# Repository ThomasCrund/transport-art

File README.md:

# Transport Art

This project is a wall-mounted transport map artwork.

The physical idea is:
- a black acrylic front layer cut as the outline of local streets
- rigid LED PCB sections mounted behind the acrylic
- flexible PCB links between sections at joints
- wall standoffs that space the whole assembly off the wall so the LEDs throw light onto the wall behind

The intent is to show live bus and light rail positions as light moving through the street network.

## Current Repository Layout

### Active work

- `CustomisableLEDStraight/`
  - Current straight LED PCB design work.
  - Uses WS2812-style addressable LEDs and connector-based chaining.

- `adaptor board/`
  - Adapter / interconnect board work related to the PCB connection system.

- `testingstencil/`
  - Stencil-related PCB project for assembly/testing.

- `transportmapwebhelper/`
  - Map planning assets and helper tooling.
  - Contains the street SVG and a React webapp used to inspect and edit the map layout, PCB placement, joints, and LED chains.

- `code/rust-realtime-vehicle/`
  - Rust service that fetches NSW GTFS realtime vehicle positions and exposes them over HTTP.
  - Currently serves `/positions` on port `3000`.

- `code/grpc-realtime-node/`
  - Earlier Node prototype for fetching GTFS realtime data.

### Old testing projects

These folders are old test projects and not the current design direction:

- `3332_16mm/`
- `3332_25mm_v2/`
- `5050_16mm/`
- `5050_20mm/`
- `5050_25mm/`
- `ConnectorsTesting/`

## Map / Planning Workflow

The map geometry appears to flow like this:

1. Street and layout artwork is created in Illustrator / DXF / SVG form.
2. `transportmapwebhelper/streetsv2consistentangles.svg` is parsed by `transportmapwebhelper/webapp/scripts/parse-svg.ts`.
3. That script generates `transportmapwebhelper/webapp/public/map_data.json`.
4. The React webapp loads that JSON and lets you inspect:
   - streets selected for LEDs
   - PCB segments
   - LED positions
   - joints between segments
   - logical LED chain routing
5. Chain assignments are saved to `transportmapwebhelper/webapp/public/chain_config.json`.

Based on the current saved data:

- `317` street paths are present
- `21` streets are marked as LED streets
- `86` PCB segments are defined
- `86` joints are defined
- `228` total LEDs are planned
- PCB segment sizes currently span `1` to `5` LEDs
- `9` logical LED chains are currently configured

## Webapp

The planning webapp lives in `transportmapwebhelper/webapp/`.

It has two parts:

- Vite/React frontend
- small Express API used to save `map_data.json` and `chain_config.json`

Useful files:

- `transportmapwebhelper/webapp/src/components/TransportMap.tsx`
- `transportmapwebhelper/webapp/src/hooks/useMapData.ts`
- `transportmapwebhelper/webapp/src/hooks/useChainConfig.ts`
- `transportmapwebhelper/webapp/server.js`

Typical local run:

```bash
cd transportmapwebhelper/webapp
npm install
npm run dev
```

That starts:

- the frontend dev server
- the local save/load API on port `3001`

## Realtime Vehicle Data

The most complete realtime data service currently in the repo is:

- `code/rust-realtime-vehicle/`

It:

- fetches NSW GTFS realtime vehicle positions
- currently requests both buses and CBD/South East light rail
- returns a simplified JSON list of vehicles with:
  - vehicle type
  - latitude / longitude
  - speed
  - bearing
  - route id

Typical local run:

```bash
cd code/rust-realtime-vehicle
cargo run
```

## CAD / Artwork Files

Top-level art and export files include:

- `streets.ai`
- `streets.dxf`
- `streetsv2consistentangles.ai`
- `streetsv2consistentangles.dxf`
- `final-lines.dxf`
- `final-linesv2.dxf`

There are also QGIS sidecar files:

- `lines-1.qmd`
- `lines-2.qmd`

## Current Gaps

From the current repo state, a few parts still appear to be incomplete or external to this repository:

- final controller firmware that drives the installed LEDs
- the mapping layer from live vehicle positions to specific PCB/LED indices
- 3D models for wall standoffs / mounting hardware
- final flexible PCB designs for all inter-joint links

## Notes

- Some transport API credentials are currently hardcoded in the prototype/realtime code and should eventually be moved to environment variables.
- The webapp and generated JSON files are currently the clearest representation of the planned wall layout.

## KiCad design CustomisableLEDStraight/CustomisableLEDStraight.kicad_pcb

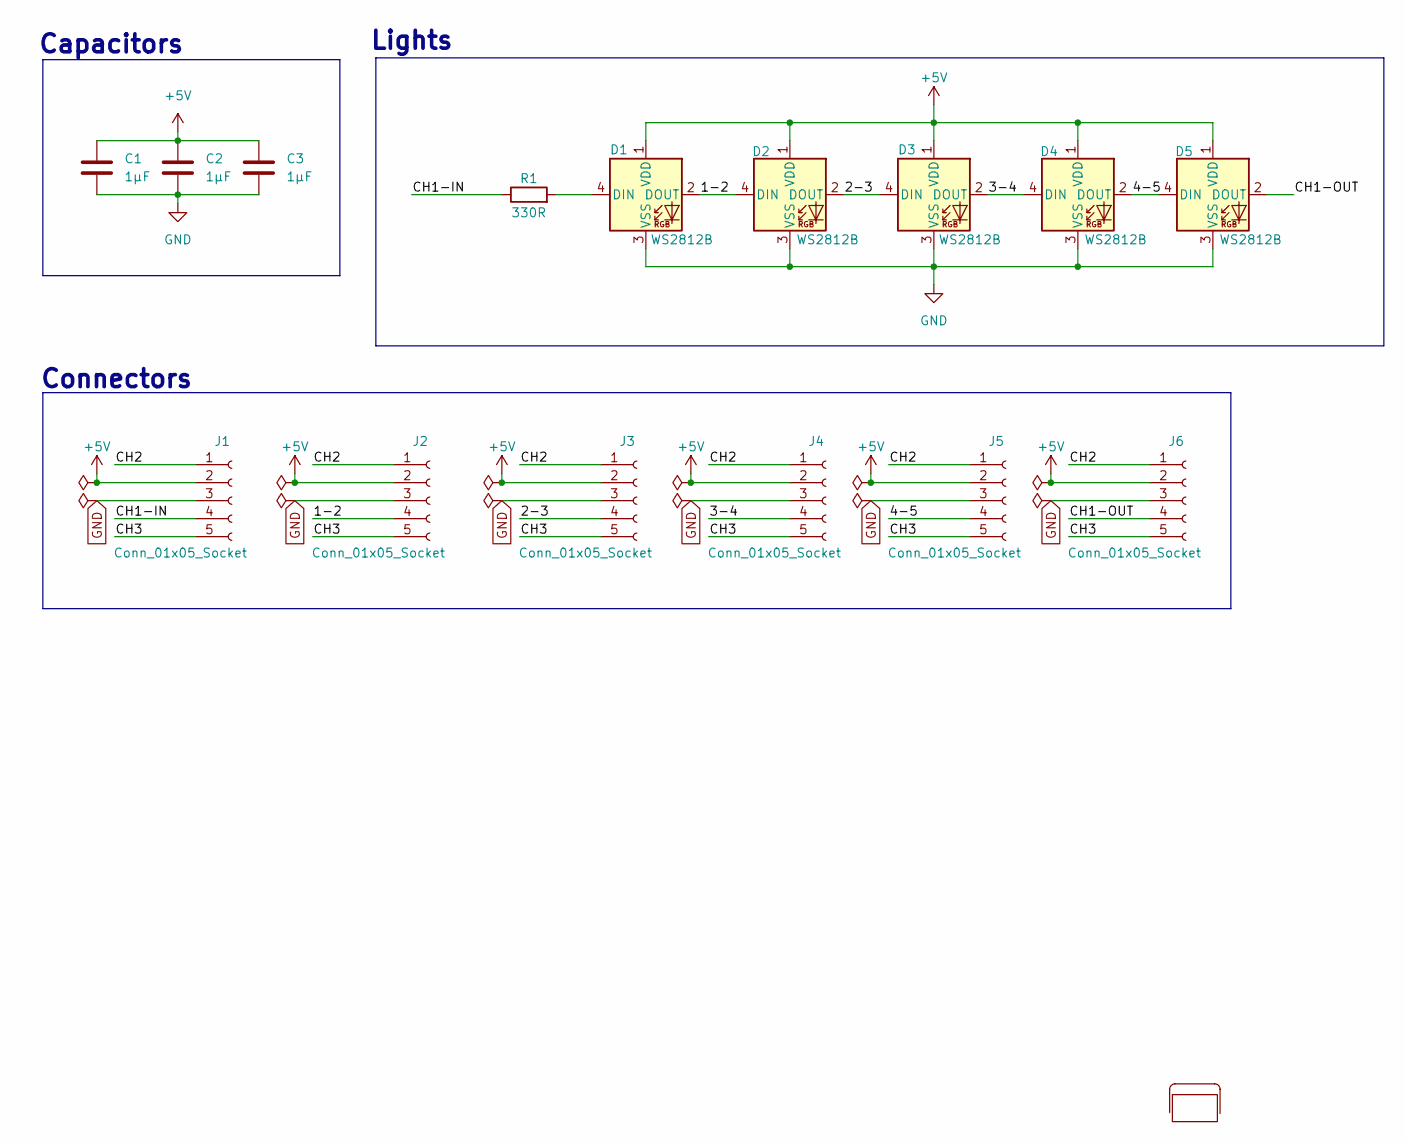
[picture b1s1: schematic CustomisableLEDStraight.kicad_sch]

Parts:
C1, C2, C3: 1µF; C_0603_1608Metric
D1, D2, D3, D4, D5: WS2812B; XL-3332RGBC-WS2812B
ESKI1: Eski_Logo
J1, J6: Conn_01x05_Socket; TransportMapConnector_half
J2, J3, J4, J5: Conn_01x05_Socket; TransportMapConnector
R1: 330R; R_0603_1608Metric

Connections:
+5V: C1.2, C2.2, C3.2, D1.1 (VDD), D2.1 (VDD), D3.1 (VDD), D4.1 (VDD), D5.1 (VDD), J1.2, J2.2, J3.2, J4.2, J5.2, J6.2
/1-2: D1.2 (DOUT), D2.4 (DIN), J2.4
/2-3: D2.2 (DOUT), D3.4 (DIN), J3.4
/3-4: D3.2 (DOUT), D4.4 (DIN), J4.4
/4-5: D4.2 (DOUT), D5.4 (DIN), J5.4
/CH1-IN: J1.4, R1.1
/CH1-OUT: D5.2 (DOUT), J6.4
/CH2: J1.1, J2.1, J3.1, J4.1, J5.1, J6.1
/CH3: J1.5, J2.5, J3.5, J4.5, J5.5, J6.5
GND: C1.1, C2.1, C3.1, D1.3 (VSS), D2.3 (VSS), D3.3 (VSS), D4.3 (VSS), D5.3 (VSS), J1.3, J2.3, J3.3, J4.3, J5.3, J6.3
unnamed: D1.4 (DIN), R1.2

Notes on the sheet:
Lights
Connectors
Capacitors

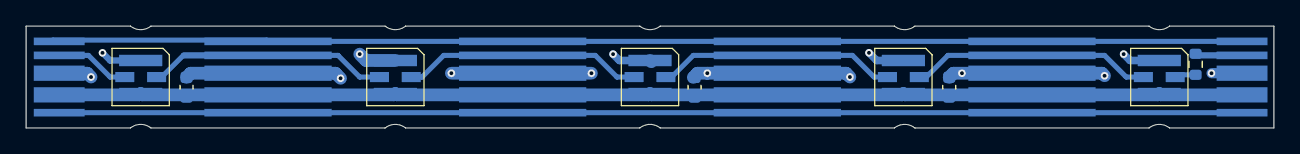
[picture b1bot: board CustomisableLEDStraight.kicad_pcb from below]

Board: 2 copper layers, 98.0 x 8.0 mm, 16 parts (15 on the bottom side), 11 nets.

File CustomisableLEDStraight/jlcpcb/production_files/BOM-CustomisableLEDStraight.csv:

Comment,Designator,Footprint,LCSC,Quantity
Conn_01x05_Socket,J2,TransportMapConnector,,1
Conn_01x05_Socket,J1,TransportMapConnector_half,,1
WS2812B,D5,XL-3332RGBC-WS2812B,,1
1µF,C2,C_0603_1608Metric,,1
WS2812B,D3,XL-3332RGBC-WS2812B,,1
WS2812B,D2,XL-3332RGBC-WS2812B,,1
1µF,C3,C_0603_1608Metric,,1
WS2812B,D4,XL-3332RGBC-WS2812B,,1
1µF,C1,C_0603_1608Metric,,1
WS2812B,D1,XL-3332RGBC-WS2812B,,1
330R,R1,R_0603_1608Metric,,1
Conn_01x05_Socket,J6,TransportMapConnector_half,,1
Conn_01x05_Socket,J5,TransportMapConnector,,1
Conn_01x05_Socket,J4,TransportMapConnector,,1
Conn_01x05_Socket,J3,TransportMapConnector,,1

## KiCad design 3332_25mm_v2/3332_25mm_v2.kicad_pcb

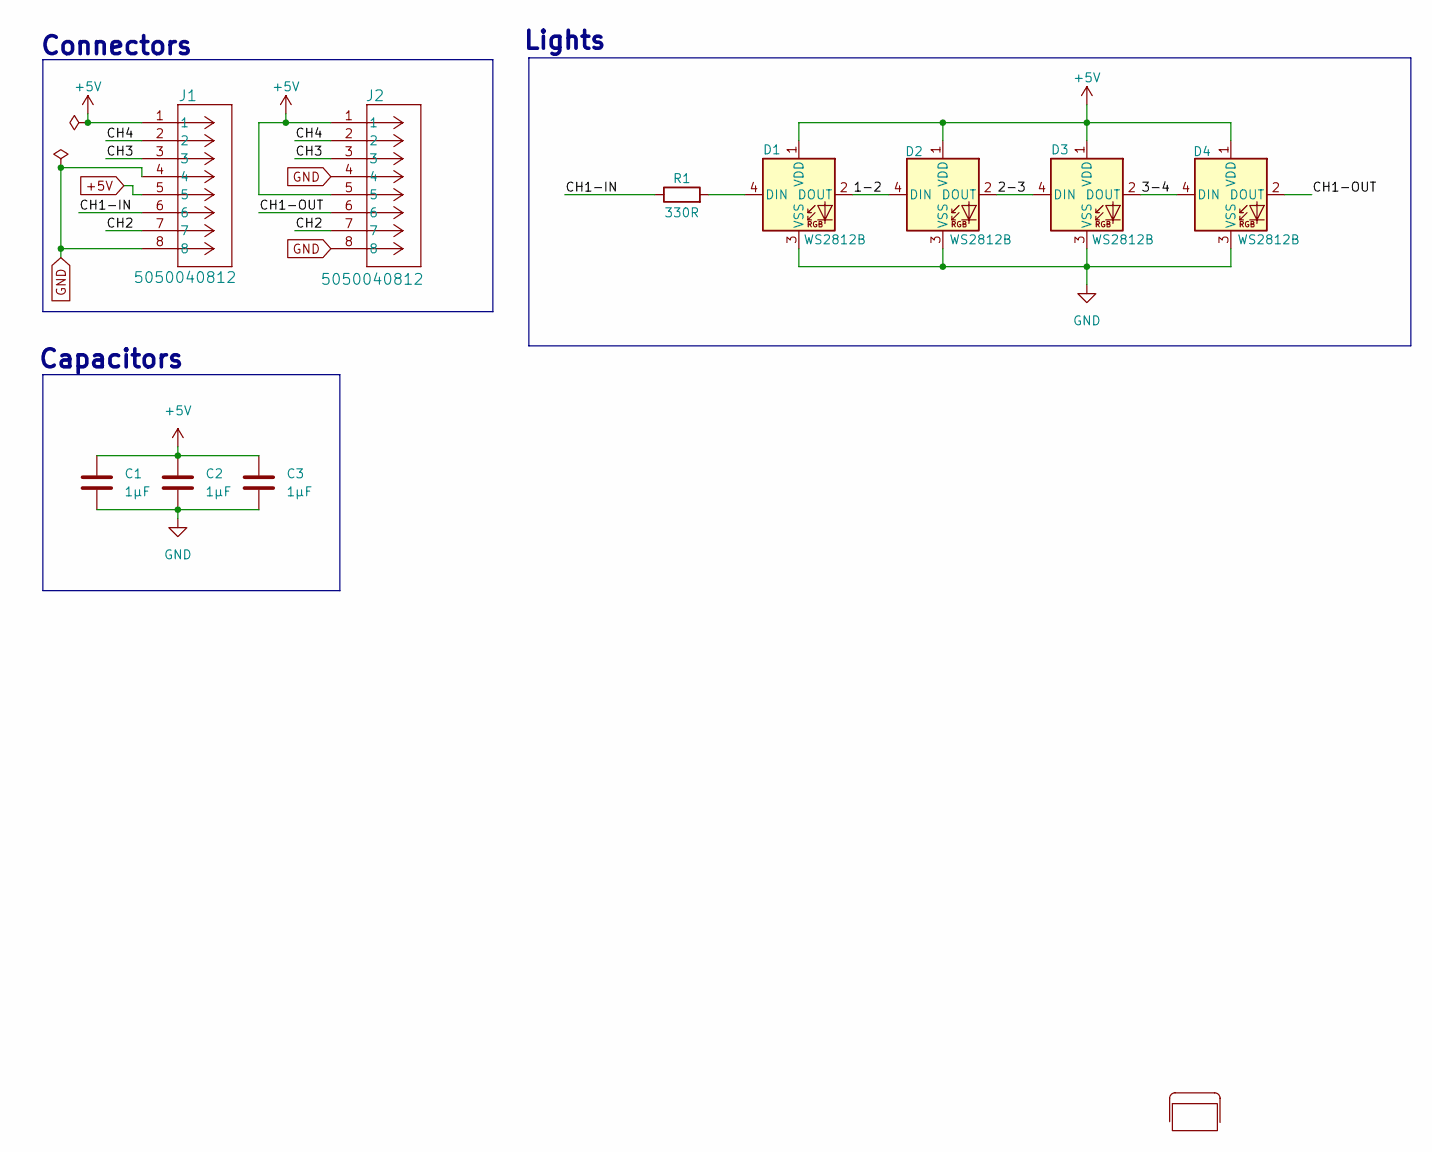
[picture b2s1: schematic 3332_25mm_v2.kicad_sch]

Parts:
C1, C2, C3: 1µF; C_0603_1608Metric
D1, D2, D3, D4: WS2812B; XL-3332RGBC-WS2812B
ESKI1: Eski_Logo
J1, J2: 5050040812; CONN8_505004-0812_MOL
R1: 330R; R_0603_1608Metric

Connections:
+5V: C1.2, C2.2, C3.2, D1.1 (VDD), D2.1 (VDD), D3.1 (VDD), D4.1 (VDD), J1.1, J1.5, J2.1, J2.5
/1-2: D1.2 (DOUT), D2.4 (DIN)
/2-3: D2.2 (DOUT), D3.4 (DIN)
/3-4: D3.2 (DOUT), D4.4 (DIN)
/CH1-IN: J1.6, R1.1
/CH1-OUT: D4.2 (DOUT), J2.6
/CH2: J1.7, J2.7
/CH3: J1.3, J2.3
/CH4: J1.2, J2.2
GND: C1.1, C2.1, C3.1, D1.3 (VSS), D2.3 (VSS), D3.3 (VSS), D4.3 (VSS), J1.4, J1.8, J2.4, J2.8
unnamed: D1.4 (DIN), R1.2

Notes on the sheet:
Connectors
Lights
Capacitors

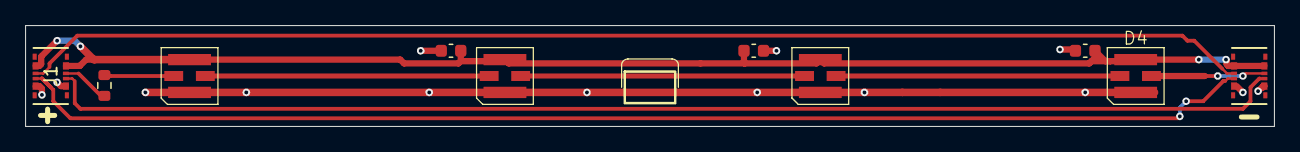
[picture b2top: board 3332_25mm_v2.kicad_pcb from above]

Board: 2 copper layers, 99.0 x 8.0 mm, 11 parts (0 on the bottom side), 11 nets.

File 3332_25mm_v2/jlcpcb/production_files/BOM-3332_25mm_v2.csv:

Comment,Designator,Footprint,LCSC,Quantity
5050040812,J2,CONN8_505004-0812_MOL,,1
5050040812,J1,CONN8_505004-0812_MOL,,1
1µF,C2,C_0603_1608Metric,,1
WS2812B,D3,XL-3332RGBC-WS2812B,,1
WS2812B,D2,XL-3332RGBC-WS2812B,,1
1µF,C3,C_0603_1608Metric,,1
WS2812B,D4,XL-3332RGBC-WS2812B,,1
1µF,C1,C_0603_1608Metric,,1
WS2812B,D1,XL-3332RGBC-WS2812B,,1
330R,R1,R_0603_1608Metric,,1

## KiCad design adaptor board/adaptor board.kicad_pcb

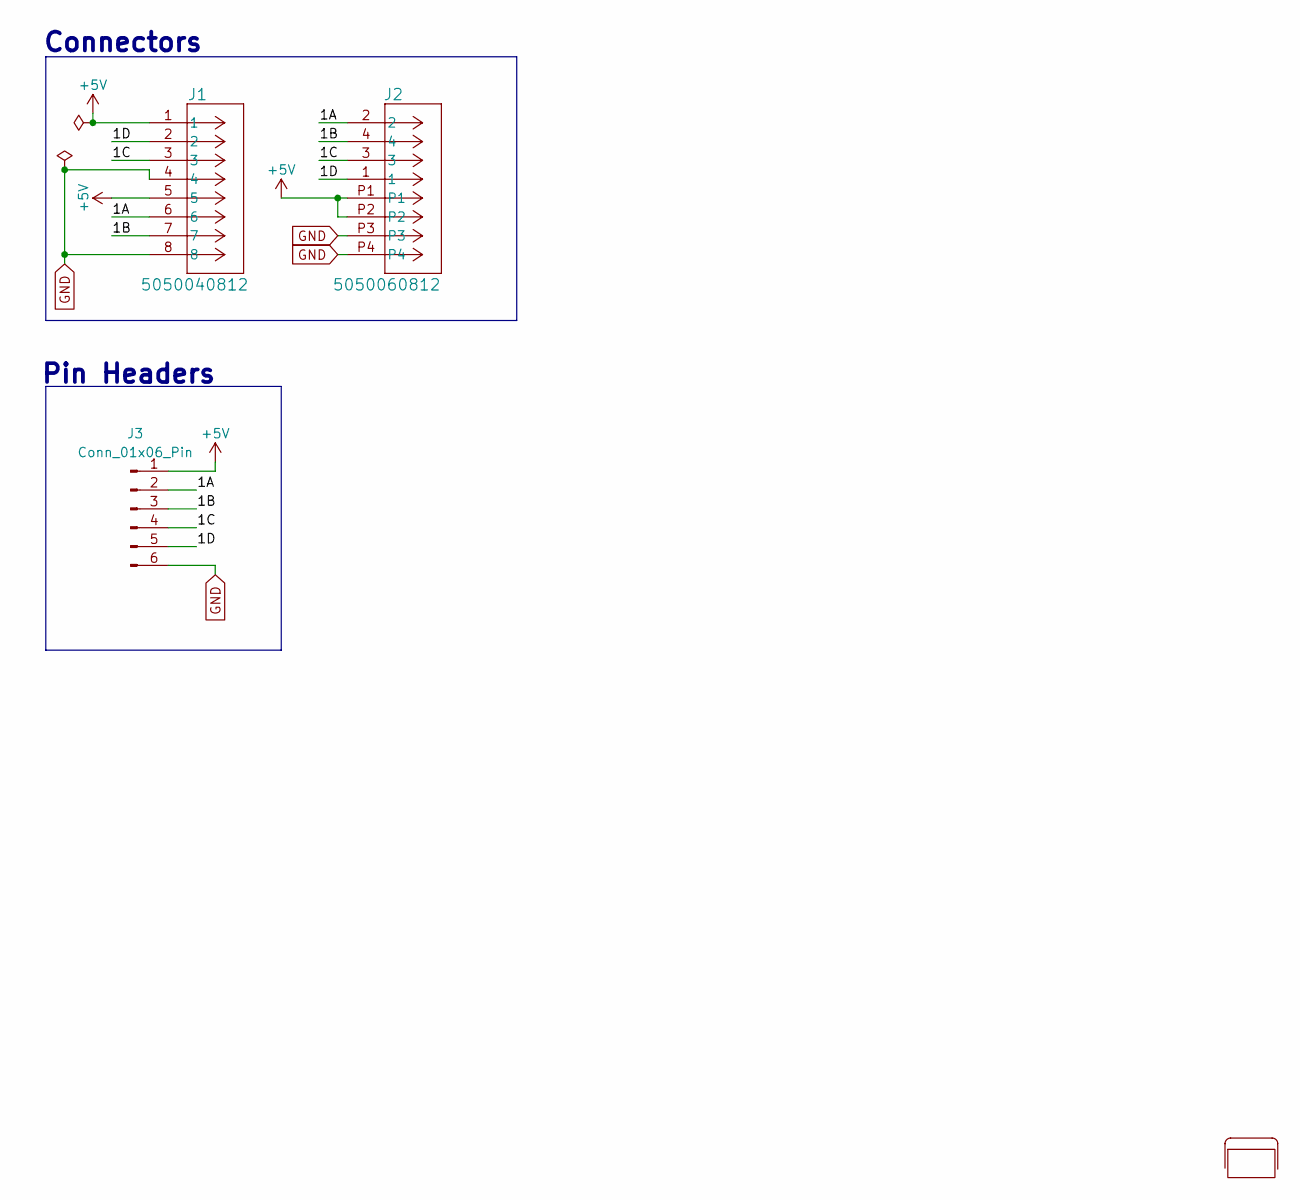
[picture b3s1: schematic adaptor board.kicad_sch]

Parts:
ESKI1: Eski_Logo
J1: 5050040812; CONN8_505004-0812_MOL
J2: 5050060812; CONN_505006-0812_MOL
J3: Conn_01x06_Pin; PinHeader_1x06_P2.54mm_Vertical

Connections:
+5V: J1.1, J1.5, J2.P1, J2.P2, J3.1
/1A: J1.6, J2.2, J3.2
/1B: J1.7, J2.4, J3.3
/1C: J1.3, J2.3, J3.4
/1D: J1.2, J2.1, J3.5
GND: J1.4, J1.8, J2.P3, J2.P4, J3.6

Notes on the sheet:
Pin Headers
Connectors

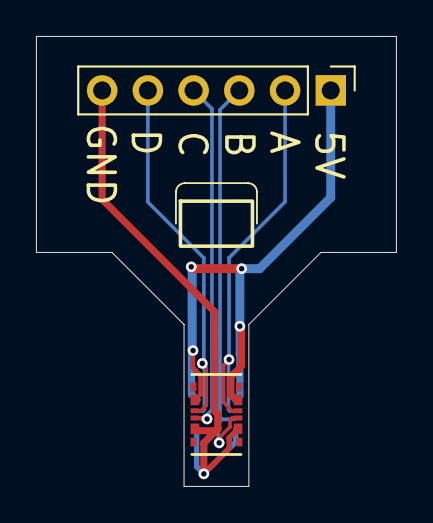
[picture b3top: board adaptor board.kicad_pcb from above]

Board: 2 copper layers, 20.0 x 25.0 mm, 4 parts (1 on the bottom side), 6 nets.

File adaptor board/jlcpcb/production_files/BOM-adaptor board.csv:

Comment,Designator,Footprint,LCSC,Quantity
5050040812,J1,CONN8_505004-0812_MOL,C724121,1
5050060812,J2,CONN_505006-0812_MOL,C779875,1
Conn_01x06_Pin,J3,PinHeader_1x06_P2.54mm_Vertical,,1

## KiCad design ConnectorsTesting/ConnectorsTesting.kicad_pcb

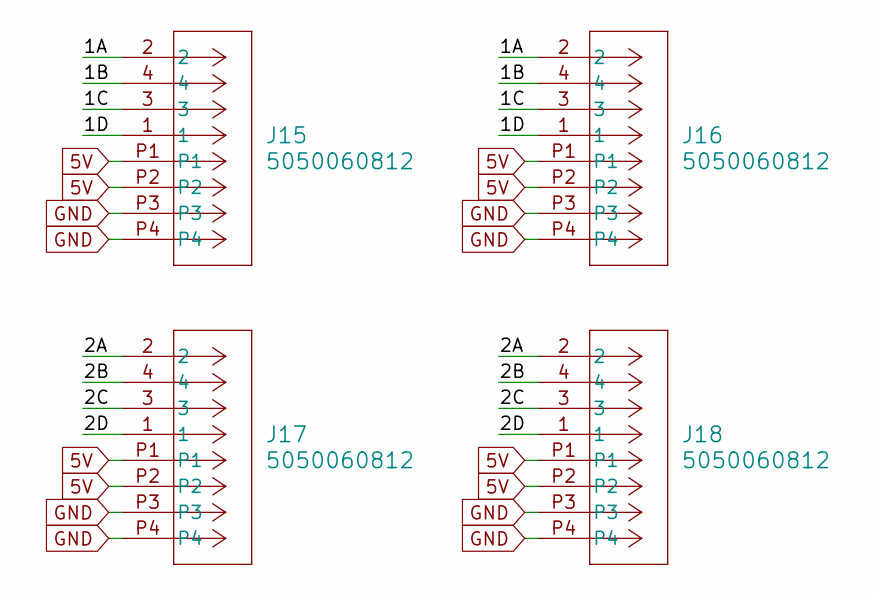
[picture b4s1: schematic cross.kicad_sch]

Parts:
J15, J16, J17, J18: 5050060812; CONN_505006-0812_MOL

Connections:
5V: J15.P1, J15.P2, J16.P1, J16.P2, J17.P1, J17.P2, J18.P1, J18.P2; also elsewhere on the board
/Cross/1A: J15.2, J16.2
/Cross/1B: J15.4, J16.4
/Cross/1C: J15.3, J16.3
/Cross/1D: J15.1, J16.1
/Cross/2A: J17.2, J18.2
/Cross/2B: J17.4, J18.4
/Cross/2C: J17.3, J18.3
/Cross/2D: J17.1, J18.1
GND: J15.P3, J15.P4, J16.P3, J16.P4, J17.P3, J17.P4, J18.P3, J18.P4; also elsewhere on the board

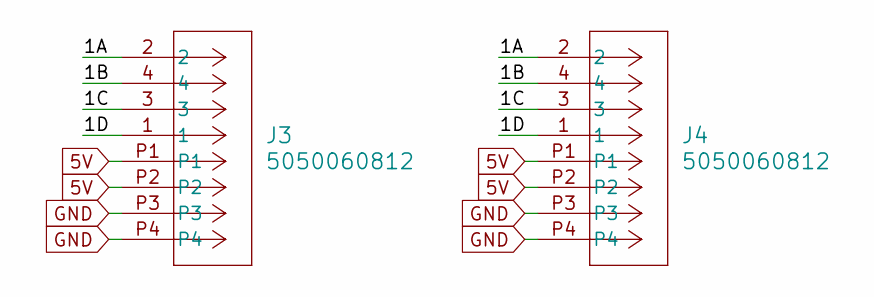
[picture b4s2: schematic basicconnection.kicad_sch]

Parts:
J3, J4: 5050060812; CONN_505006-0812_MOL

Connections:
5V: J3.P1, J3.P2, J4.P1, J4.P2; also elsewhere on the board
/Basic1-1/1A: J3.2, J4.2
/Basic1-1/1B: J3.4, J4.4
/Basic1-1/1C: J3.3, J4.3
/Basic1-1/1D: J3.1, J4.1
GND: J3.P3, J3.P4, J4.P3, J4.P4; also elsewhere on the board

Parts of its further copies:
J19, J20, J21, J22, J23, J24, J25, J26: 5050060812; CONN_505006-0812_MOL

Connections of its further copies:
5V: J19.P1, J19.P2, J20.P1, J20.P2, J21.P1, J21.P2, J22.P1, J22.P2, J23.P1, J23.P2, J24.P1, J24.P2, J25.P1, J25.P2, J26.P1, J26.P2; also elsewhere on the board
/Basic1-1-curve1/1A: J19.2, J20.2
/Basic1-1-curve1/1B: J19.4, J20.4
/Basic1-1-curve1/1C: J19.3, J20.3
/Basic1-1-curve1/1D: J19.1, J20.1
/Basic1-1-curve-2/1A: J21.2, J22.2
/Basic1-1-curve-2/1B: J21.4, J22.4
/Basic1-1-curve-2/1C: J21.3, J22.3
/Basic1-1-curve-2/1D: J21.1, J22.1
/Basic1-2-extension2/1A: J25.2, J26.2
/Basic1-2-extension2/1B: J25.4, J26.4
/Basic1-2-extension2/1C: J25.3, J26.3
/Basic1-2-extension2/1D: J25.1, J26.1
/Basic1-2-extension/1A: J23.2, J24.2
/Basic1-2-extension/1B: J23.4, J24.4
/Basic1-2-extension/1C: J23.3, J24.3
/Basic1-2-extension/1D: J23.1, J24.1
GND: J19.P3, J19.P4, J20.P3, J20.P4, J21.P3, J21.P4, J22.P3, J22.P4, J23.P3, J23.P4, J24.P3, J24.P4, J25.P3, J25.P4, J26.P3, J26.P4; also elsewhere on the board

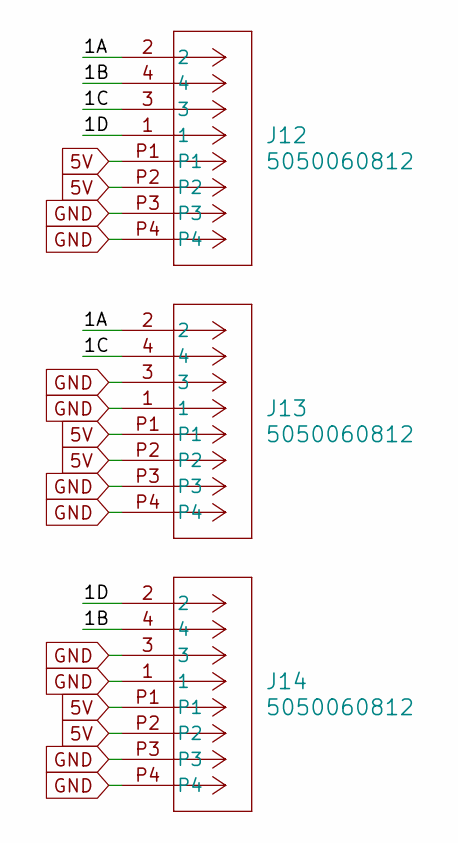
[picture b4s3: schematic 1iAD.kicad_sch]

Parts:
J12, J13, J14: 5050060812; CONN_505006-0812_MOL

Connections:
5V: J12.P1, J12.P2, J13.P1, J13.P2, J14.P1, J14.P2; also elsewhere on the board
/1Input;Output(A,D)/1A: J12.2, J13.2
/1Input;Output(A,D)/1B: J12.4, J14.4
/1Input;Output(A,D)/1C: J12.3, J13.4
/1Input;Output(A,D)/1D: J12.1, J14.2
GND: J12.P3, J12.P4, J13.1, J13.3, J13.P3, J13.P4, J14.1, J14.3, J14.P3, J14.P4; also elsewhere on the board

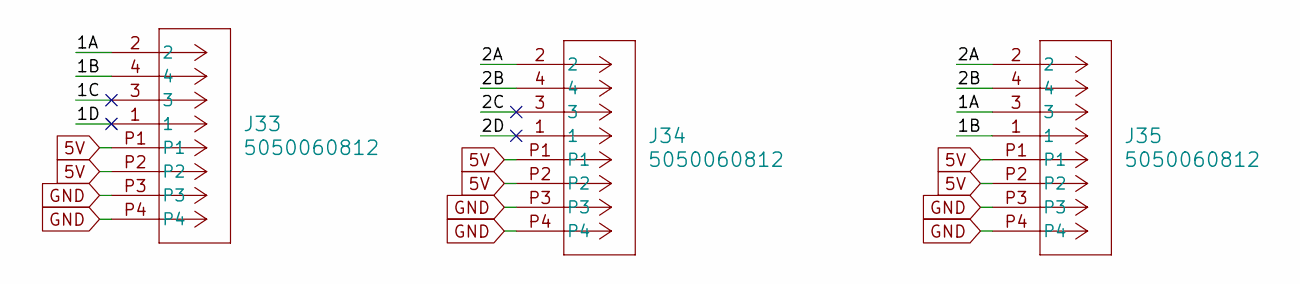
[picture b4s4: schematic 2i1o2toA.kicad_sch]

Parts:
J33, J34, J35: 5050060812; CONN_505006-0812_MOL

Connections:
5V: J33.P1, J33.P2, J34.P1, J34.P2, J35.P1, J35.P2; also elsewhere on the board
/2Input1Output2ToA/1A: J33.2, J35.3
/2Input1Output2ToA/1B: J33.4, J35.1
/2Input1Output2ToA/1C: J33.3
/2Input1Output2ToA/1D: J33.1
/2Input1Output2ToA/2A: J34.2, J35.2
/2Input1Output2ToA/2B: J34.4, J35.4
/2Input1Output2ToA/2C: J34.3
/2Input1Output2ToA/2D: J34.1
GND: J33.P3, J33.P4, J34.P3, J34.P4, J35.P3, J35.P4; also elsewhere on the board

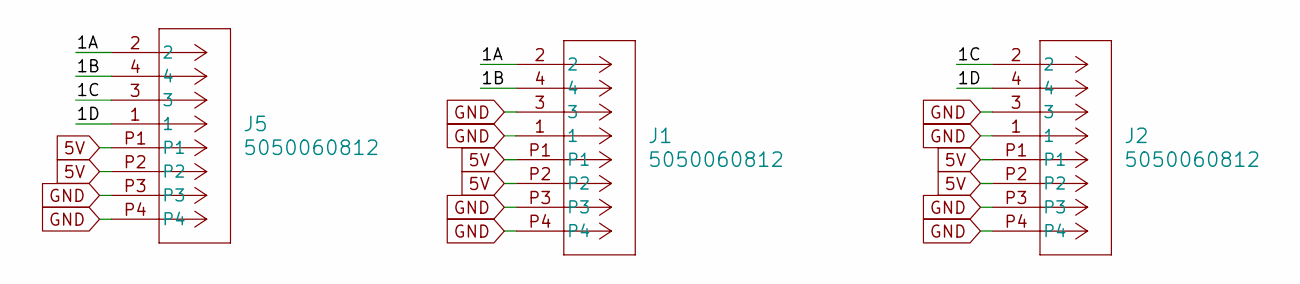
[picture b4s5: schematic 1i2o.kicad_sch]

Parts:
J1, J2, J5: 5050060812; CONN_505006-0812_MOL

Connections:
5V: J1.P1, J1.P2, J2.P1, J2.P2, J5.P1, J5.P2; also elsewhere on the board
/1Input2Outputs/1A: J1.2, J5.2
/1Input2Outputs/1B: J1.4, J5.4
/1Input2Outputs/1C: J2.2, J5.3
/1Input2Outputs/1D: J2.4, J5.1
GND: J1.1, J1.3, J1.P3, J1.P4, J2.1, J2.3, J2.P3, J2.P4, J5.P3, J5.P4; also elsewhere on the board

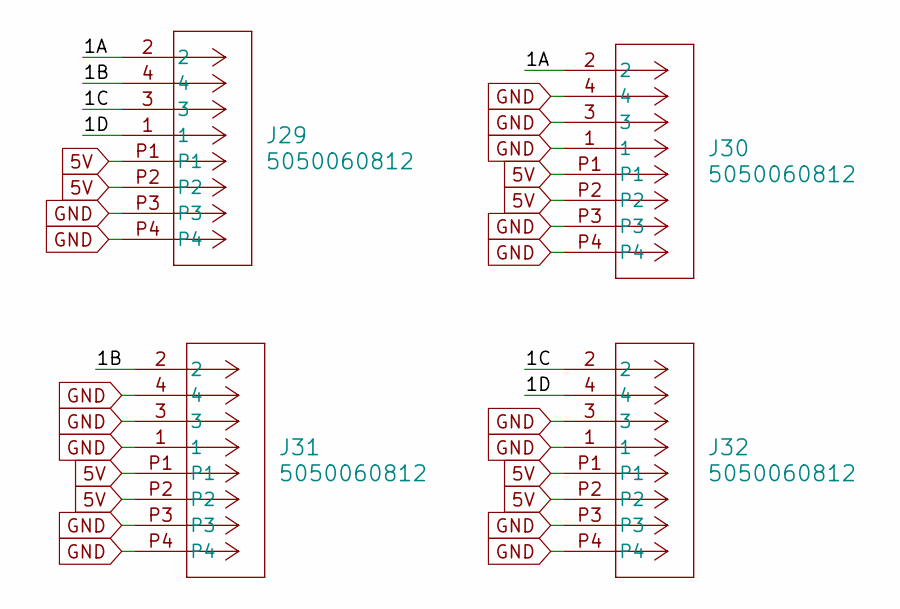
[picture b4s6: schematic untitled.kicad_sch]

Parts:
J29, J30, J31, J32: 5050060812; CONN_505006-0812_MOL

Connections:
5V: J29.P1, J29.P2, J30.P1, J30.P2, J31.P1, J31.P2, J32.P1, J32.P2; also elsewhere on the board
/1Input3Output/1A: J29.2, J30.2
/1Input3Output/1B: J29.4, J31.2
/1Input3Output/1C: J29.3, J32.2
/1Input3Output/1D: J29.1, J32.4
GND: J29.P3, J29.P4, J30.1, J30.3, J30.4, J30.P3, J30.P4, J31.1, J31.3, J31.4, J31.P3, J31.P4, J32.1, J32.3, J32.P3, J32.P4; also elsewhere on the board

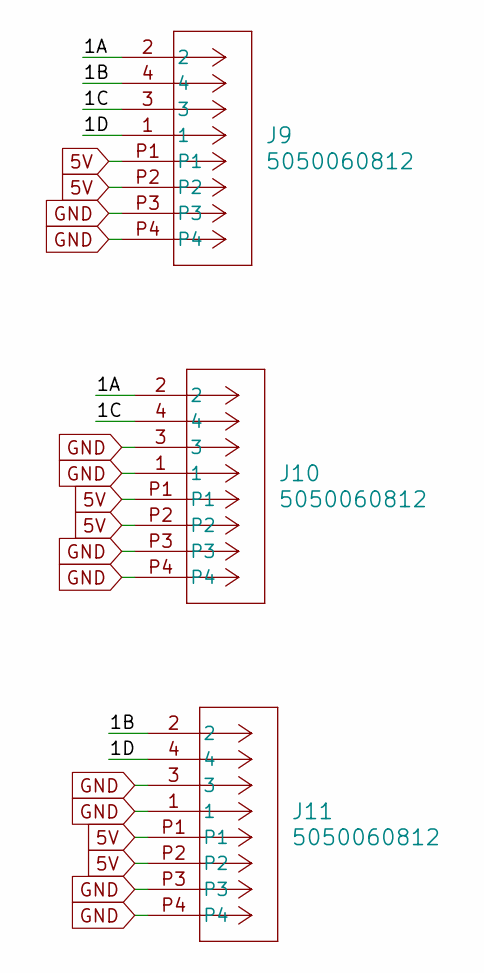
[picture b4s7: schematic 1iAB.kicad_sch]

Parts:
J9, J10, J11: 5050060812; CONN_505006-0812_MOL

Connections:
5V: J9.P1, J9.P2, J10.P1, J10.P2, J11.P1, J11.P2; also elsewhere on the board
/1nput;Output(A,B)/1A: J9.2, J10.2
/1nput;Output(A,B)/1B: J9.4, J11.2
/1nput;Output(A,B)/1C: J9.3, J10.4
/1nput;Output(A,B)/1D: J9.1, J11.4
GND: J9.P3, J9.P4, J10.1, J10.3, J10.P3, J10.P4, J11.1, J11.3, J11.P3, J11.P4; also elsewhere on the board

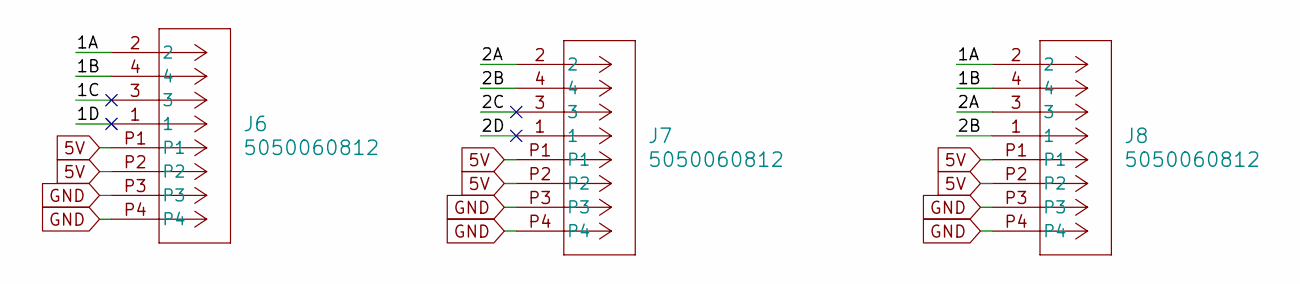
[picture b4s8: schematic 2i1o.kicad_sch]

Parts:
J6, J7, J8: 5050060812; CONN_505006-0812_MOL

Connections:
5V: J6.P1, J6.P2, J7.P1, J7.P2, J8.P1, J8.P2; also elsewhere on the board
/2Inputs1Output/1A: J6.2, J8.2
/2Inputs1Output/1B: J6.4, J8.4
/2Inputs1Output/1C: J6.3
/2Inputs1Output/1D: J6.1
/2Inputs1Output/2A: J7.2, J8.3
/2Inputs1Output/2B: J7.4, J8.1
/2Inputs1Output/2C: J7.3
/2Inputs1Output/2D: J7.1
GND: J6.P3, J6.P4, J7.P3, J7.P4, J8.P3, J8.P4; also elsewhere on the board

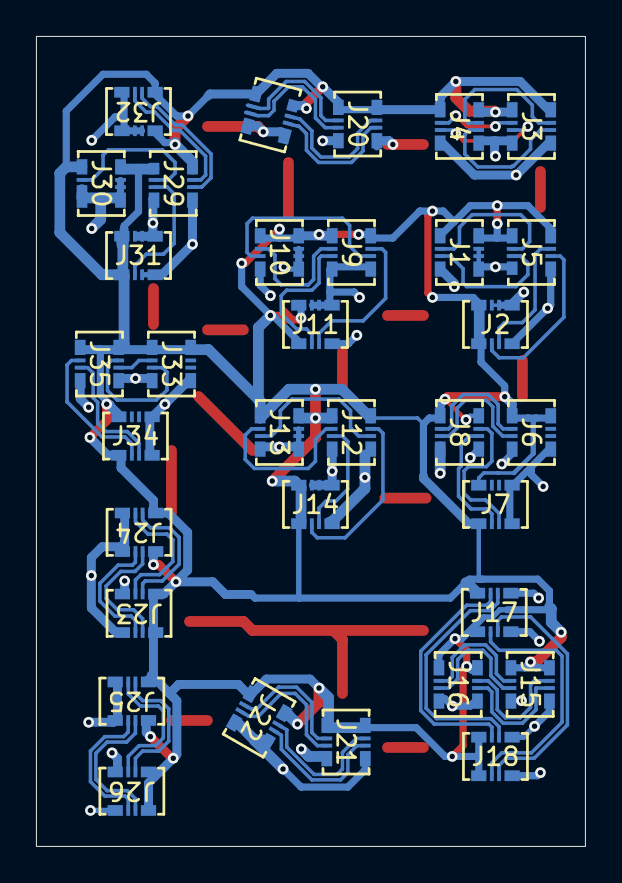
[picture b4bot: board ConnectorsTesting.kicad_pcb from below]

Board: 2 copper layers, 30.5 x 45.0 mm, 33 parts (33 on the bottom side), 54 nets.

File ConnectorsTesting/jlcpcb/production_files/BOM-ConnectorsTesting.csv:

Comment,Designator,Footprint,LCSC,Quantity
5050060812,J22,CONN_505006-0812_MOL,,1
5050060812,J12,CONN_505006-0812_MOL,,1
5050060812,J5,CONN_505006-0812_MOL,,1
5050060812,J26,CONN_505006-0812_MOL,,1
5050060812,J15,CONN_505006-0812_MOL,,1
5050060812,J35,CONN_505006-0812_MOL,,1
5050060812,J27,CONN_505006-0812_MOL,,1
5050060812,J9,CONN_505006-0812_MOL,,1
5050060812,J14,CONN_505006-0812_MOL,,1
5050060812,J3,CONN_505006-0812_MOL,,1
5050060812,J11,CONN_505006-0812_MOL,,1
5050060812,J17,CONN_505006-0812_MOL,,1
5050060812,J6,CONN_505006-0812_MOL,,1
5050060812,J33,CONN_505006-0812_MOL,,1
5050060812,J34,CONN_505006-0812_MOL,,1
5050060812,J1,CONN_505006-0812_MOL,,1
5050060812,J23,CONN_505006-0812_MOL,,1
5050060812,J18,CONN_505006-0812_MOL,,1
5050060812,J2,CONN_505006-0812_MOL,,1
5050060812,J7,CONN_505006-0812_MOL,,1
5050060812,J20,CONN_505006-0812_MOL,,1
5050060812,J32,CONN_505006-0812_MOL,,1
5050060812,J4,CONN_505006-0812_MOL,,1
5050060812,J21,CONN_505006-0812_MOL,,1
5050060812,J30,CONN_505006-0812_MOL,,1
5050060812,J29,CONN_505006-0812_MOL,,1
5050060812,J13,CONN_505006-0812_MOL,,1
5050060812,J25,CONN_505006-0812_MOL,,1
5050060812,J28,CONN_505006-0812_MOL,,1
5050060812,J24,CONN_505006-0812_MOL,,1
5050060812,J16,CONN_505006-0812_MOL,,1
5050060812,J8,CONN_505006-0812_MOL,,1
5050060812,J10,CONN_505006-0812_MOL,,1
5050060812,J31,CONN_505006-0812_MOL,,1
5050060812,J19,CONN_505006-0812_MOL,,1

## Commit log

2026-03-10 Code pre git
2026-03-10 added readme to project
